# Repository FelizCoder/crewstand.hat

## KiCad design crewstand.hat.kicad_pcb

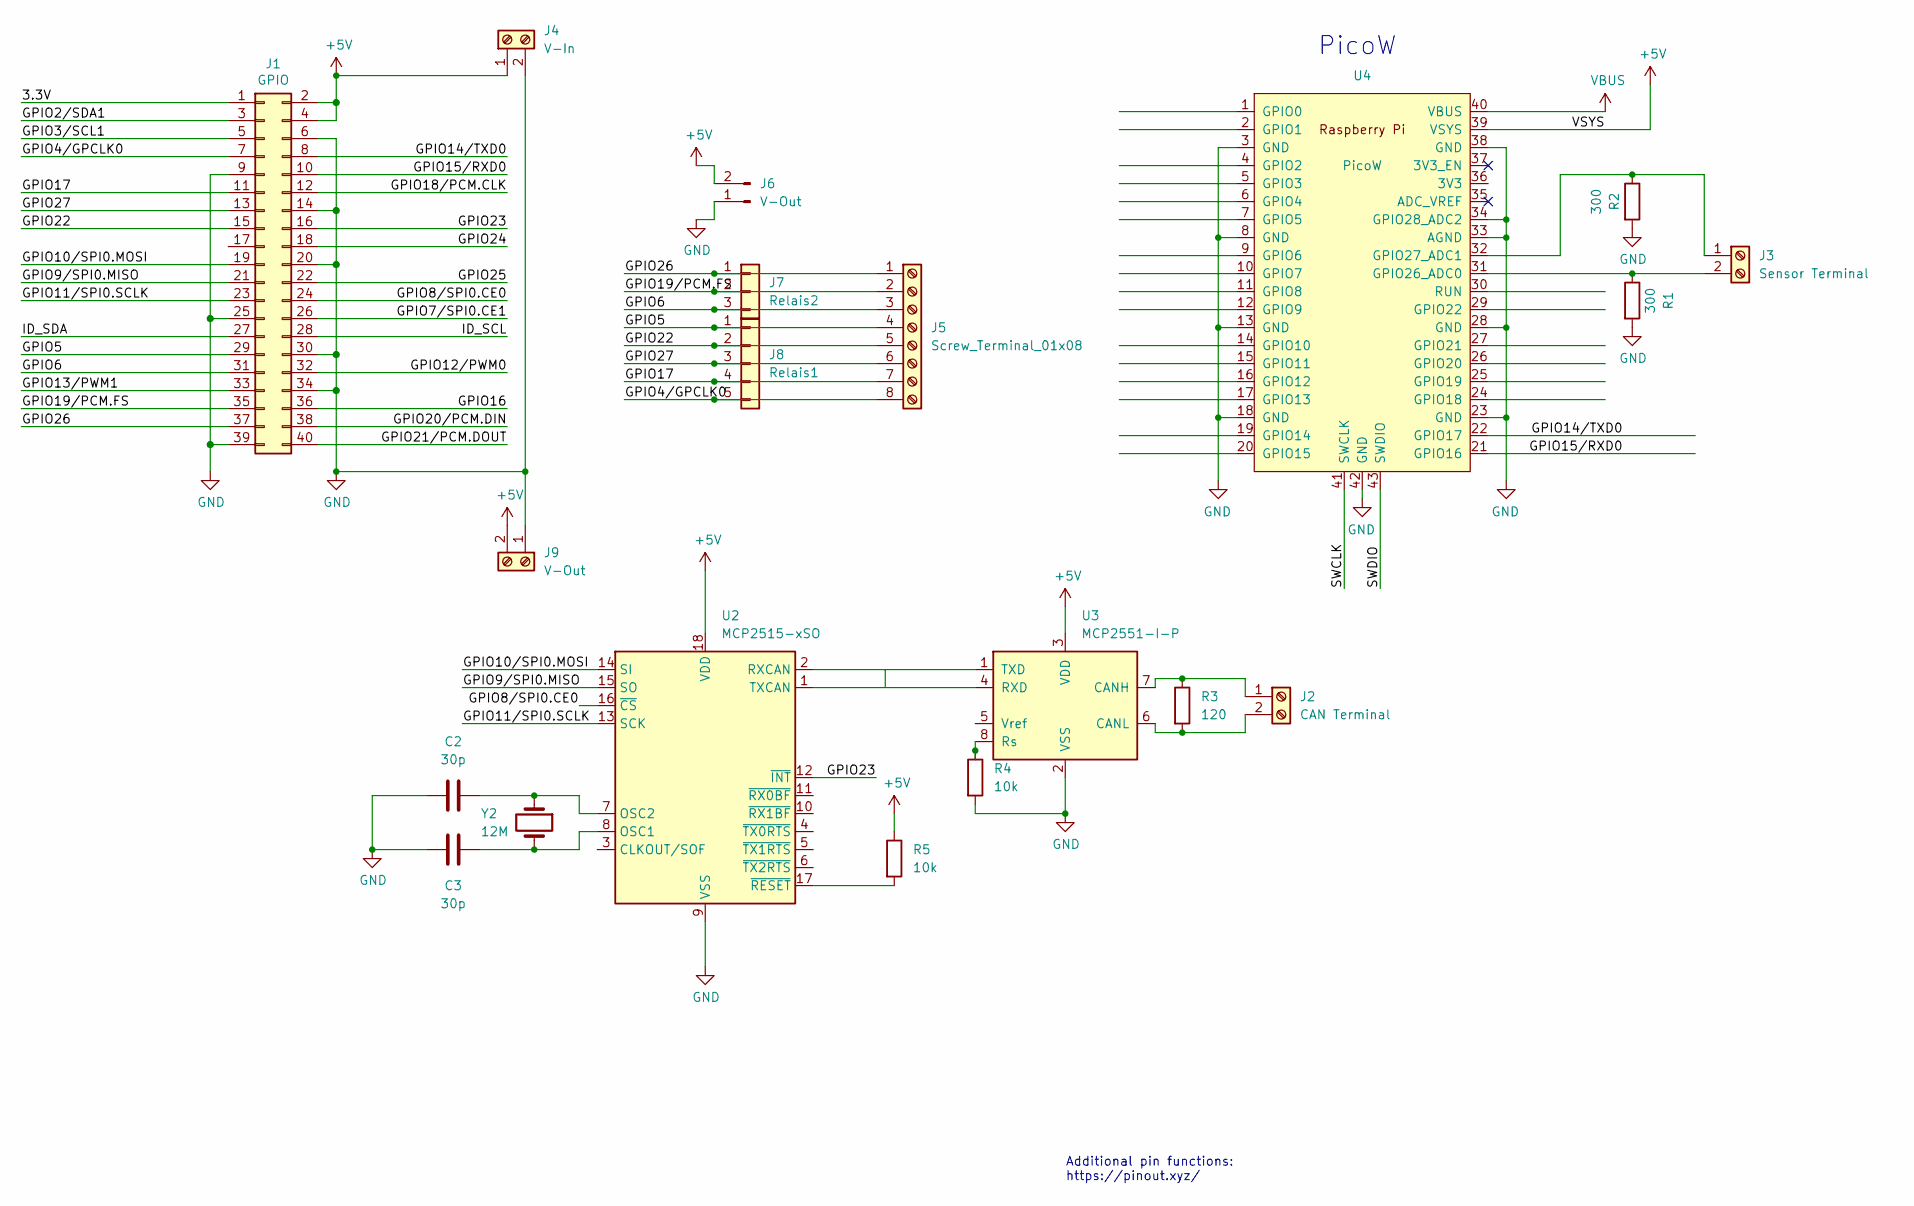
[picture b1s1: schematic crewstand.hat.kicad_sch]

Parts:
C2, C3: 30p; C_Disc_D3.4mm_W2.1mm_P2.50mm
J1: GPIO; PinSocket_2x20_P2.54mm_Vertical
J2: CAN Terminal; TerminalBlock_bornier-2_P5.08mm
J3: Sensor Terminal; TerminalBlock_bornier-2_P5.08mm
J4: V-In; TerminalBlock_bornier-2_P5.08mm
J5: Screw_Terminal_01x08; TerminalBlock_bornier-8_P5.08mm
J6: V-Out; JST_XH_B2B-XH-A_1x02_P2.50mm_Vertical
J7: Relais2; JST_XH_B3B-XH-A_1x03_P2.50mm_Vertical
J8: Relais1; JST_XH_B5B-XH-A_1x05_P2.50mm_Vertical
J9: V-Out; TerminalBlock_bornier-2_P5.08mm
R1, R2: 300; R_Axial_DIN0204_L3.6mm_D1.6mm_P5.08mm_Horizontal
R3: 120; R_Axial_DIN0204_L3.6mm_D1.6mm_P5.08mm_Horizontal
R4, R5: 10k; R_Axial_DIN0204_L3.6mm_D1.6mm_P5.08mm_Horizontal
U2: MCP2515-xSO; DIP-18_W7.62mm
U3: MCP2551-I-P; DIP-8_W7.62mm
U4: PicoW; RPi_PicoW_SMD_TH
Y2: 12M; Crystal_HC49-U_Vertical

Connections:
+5V: J1.2, J1.4, J4.1, J6.2, J9.2, R5.1, U2.18 (VDD), U3.3 (VDD), U4.39 (VSYS)
/3.3V: J1.1
/GPIO2/SDA1: J1.3
/GPIO3/SCL1: J1.5
/GPIO4/GPCLK0: J1.7, J5.8, J8.5
/GPIO5: J1.29, J5.4, J8.1
/GPIO6: J1.31, J5.3, J7.3
/GPIO7/SPI0.CE1: J1.26
/GPIO8/SPI0.CE0: J1.24, U2.16 (~CS)
/GPIO9/SPI0.MISO: J1.21, U2.15 (SO)
/GPIO10/SPI0.MOSI: J1.19, U2.14 (SI)
/GPIO11/SPI0.SCLK: J1.23, U2.13 (SCK)
/GPIO12/PWM0: J1.32
/GPIO13/PWM1: J1.33
/GPIO14/TXD0: J1.8, U4.22 (GPIO17)
/GPIO15/RXD0: J1.10, U4.21 (GPIO16)
/GPIO16: J1.36
/GPIO17: J1.11, J5.7, J8.4
/GPIO18/PCM.CLK: J1.12
/GPIO19/PCM.FS: J1.35, J5.2, J7.2
/GPIO20/PCM.DIN: J1.38
/GPIO21/PCM.DOUT: J1.40
/GPIO22: J1.15, J5.5, J8.2
/GPIO23: J1.16, U2.12 (~INT)
/GPIO24: J1.18
/GPIO25: J1.22
/GPIO26: J1.37, J5.1, J7.1
/GPIO27: J1.13, J5.6, J8.3
/ID_SCL: J1.28
/ID_SDA: J1.27
/SWCLK: U4.41 (SWCLK)
/SWDIO: U4.43 (SWDIO)
GND: C2.2, C3.2, J1.6, J1.9, J1.14, J1.20, J1.25, J1.30, J1.34, J1.39, J4.2, J6.1, J9.1, R1.2, R2.2, R4.2, U2.9 (VSS), U3.2 (VSS), U4.3 (GND), U4.8 (GND), U4.13 (GND), U4.18 (GND), U4.23 (GND), U4.28 (GND), U4.33 (AGND), U4.34 (GPIO28_ADC2), U4.38 (GND), U4.42 (GND)
unnamed: J2.1, R3.1, U3.7 (CANH)
unnamed: J2.2, R3.2, U3.6 (CANL)
unnamed: J3.1, R2.1, U4.32 (GPIO27_ADC1)
unnamed: J3.2, R1.1, U4.31 (GPIO26_ADC0)
unnamed: C3.1, U2.8 (OSC1), Y2.2
unnamed: C2.1, U2.7 (OSC2), Y2.1
unnamed: U2.2 (RXCAN), U3.1 (TXD)
unnamed: U2.1 (TXCAN), U3.4 (RXD)
unnamed: R5.2, U2.17 (~RESET)
unnamed: R4.1, U3.8 (Rs)
VBUS: U4.40 (VBUS)

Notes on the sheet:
PicoW
Additional pin functions: https://pinout.xyz/

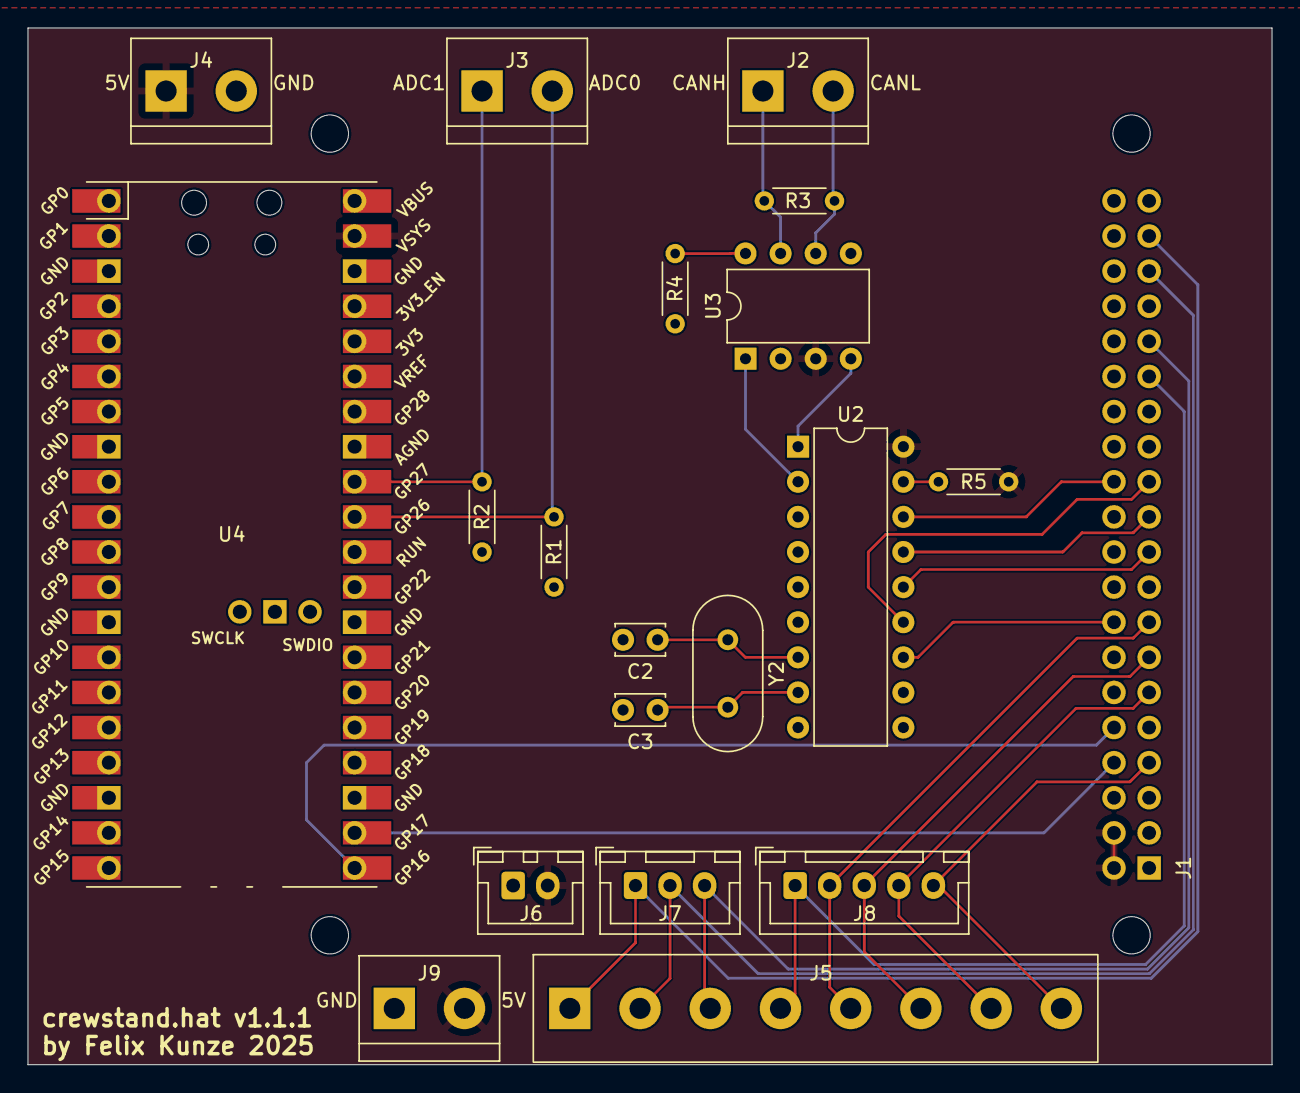
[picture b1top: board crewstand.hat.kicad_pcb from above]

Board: 2 copper layers, 90.0 x 75.0 mm, 23 parts (1 on the bottom side), 27 nets.

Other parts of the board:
MH1, MH2: MountingHole_2.7mm_M2.5
REF4: MountingHole_2.7mm_M2.5

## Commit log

2025-02-05 feat: initial design
    Release as: 0.0.0
2025-02-05 chore(main): release 1.0.0
2025-02-12 feat!: reorder for bottom placement
    * Bottom placement needed to have connectors accessible on top
    * optimize trace width
    * optimise for voroni design
    * include [pcb2gcode](https://github.com/pcb2gcode/pcb2gcode) generated svg for cnc
    BREAKING CHANGE: Platine Layout for bottom
    placement of the Parts
2025-02-12 feat: adopt voroni design
    * do not use GND fill to optimize for voroni design
    * voroni design for better milling
    * milling paths generated with [pcb2gcode](https://github.com/pcb2gcode/pcb2gcode)
2025-02-12 feat: use jst connectors
    * update clearance and track width
    * Optimize placement and tracks
    issue #2
2025-02-12 feat: add mounting holes
2025-02-12 chore: define release
    Release-As: 1.0.0
2025-02-12 fix(Sensors): correct resistor placement for analog sensor readings
    - Move pull-down resistors from sensor-to-ADC path to ADC-to-GND
    - Update schematic to implement proper current-to-voltage conversion
    Breaking Change: Yes
    - PCB layout updated
    - Existing boards will need rework to implement this fix
    Resolves: #6
2025-02-12 chore(main): release 1.0.1
2025-02-12 feat: switch to professional PCB manufacturing service
    - Update design rules for professional PCB manufacturing
    - Prepare files for PCBWay or similar manufacturer submission
    - use two layers for routing
    - use GND / 5V fill on layers
    - place silkscreen notes
    - add redundant screw terminal for relais board connection
2025-02-12 chore(main): release 1.1.0
2025-02-19 fix(relais-gpio): use GPIO26 & 19
    - GPIO 2&3 where high on boot
    - ensures all pins are low until actively switched by backend
    - minor changes on routing and footprints
    issue #13
2025-02-19 chore(main): release 1.1.1
